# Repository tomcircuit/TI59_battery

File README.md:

# TI59_battery - LiPo Battery for TI-58/59 Calculators
 
This is my attempt at a LiPo-based battery pack for Texas Instruments Calculators that use the BP01 battery pack,  specifically the TI-58, TI-58C, and TI-59. The original NiCd packs are all dead by now, and rebuilding them is difficult, mostly because it requires cutting apart and then carefully re-assembling the plastic battery retention frame. I thought it would be fun to design a 3D printed housing and re-use the circuitry from my rechargeable HP LiPo battery pack. 

> LiPo chemistry has very specific care-and-feeding when it comes to recharging, **the original charger and charging circuitry will not suffice.**  For this reason, I include a USB receptacle, which allows for charging when removed from the calculator.

The basic idea is to use a gold-flashed (ENIG) PCB as the contact substrate, and mount the LiPo, USB micro B receptacle, and charging circuitry on the opposite side. A **charging LED** is placed on the same side as the contact pads, but in areas where there will be no mechanical interference. A 3D printed plastic holder ties it all together, and mates with the TI calculator case. 
 
## The Housing
I  have several original TI BP01 battery packs, so I was able to carefully measure them and create a 3D model using OpenSCAD. This is essentially a 3D solid 'programming language' which (for me) is much easier to work with than an interactive 3D CAD program. It took several iterations to arrive at a working holder design that would 3D print (FDM) reliably. Note that the holder is best printed "flat side down", but that this orientation is **not ideal** for the retention tab; it wants to break along the FDM layers. I have had good luck with PLA+ material, and even better results with PTEG. 

## The PCB 
The PCB holds the USB micro B connector, the charging circuitry, the protection circuitry, a connector for the LiPo battery, and most importantly the pads that mate with the contacts in the calculator.  The overall size of the PCB is 53mm x 28mm. The material is 1.6mm thick FR4. So that the contact pads do not  tarnish over time, I chose a gold-flash treatment (ENIG). 

The schematic and PCB were designed using KiCAD.

## The LiPo Battery
I wanted a 1S (3.7V) LiPo battery in the neighborhood of 1200mAhr that would fit within the confines of the original pack envelope. This led me to a size "103040" LiPo battery. 

## Putting It All Together
Pretty self-explanatory. I used 0805 size components to allow for easy hand-soldering. Note that D1 (LED) and Z1 (Zener) are both polarized, so pay attention to that. Soldering the USB connector requires a fine-tip iron and some patience, or a hot-air solder station. I use the latter with very good results. 

Connect the battery to the PCB, double-checking that the polarity of the LiPo is matching the **+** and **-** marks on the PCB. Place the battery into the holder in between the two pairs of screw bosses, and then press the PCB into place above it. Four #2 self-tapping stainless steel screws secure the PCB into the 3D printed holder.

## Charge It
Connect a micro-B cable to the board and charge the LiPo battery. The LED will stay lit during the charging process, and extinguish when it is completed. The charge current is about 220mA (0.2C for a 1200mAhr battery). You can adjust R1 to change the current (decrease R1 will increase charging current) if you need to. It took about three hours to charge my battery.

## Use It!
Install the pack into the calculator. Be very careful with the delicate latch retention tab when inserting and removing the holder, because it is fragile and prone to breakage. If it does break, you can usually re-attach the tab with Krazy Glue. Enjoy using your vintage TI programmable calculator!

>February 7. 2021
>Tom LeMense
> Written with [StackEdit](https://stackedit.io/). #

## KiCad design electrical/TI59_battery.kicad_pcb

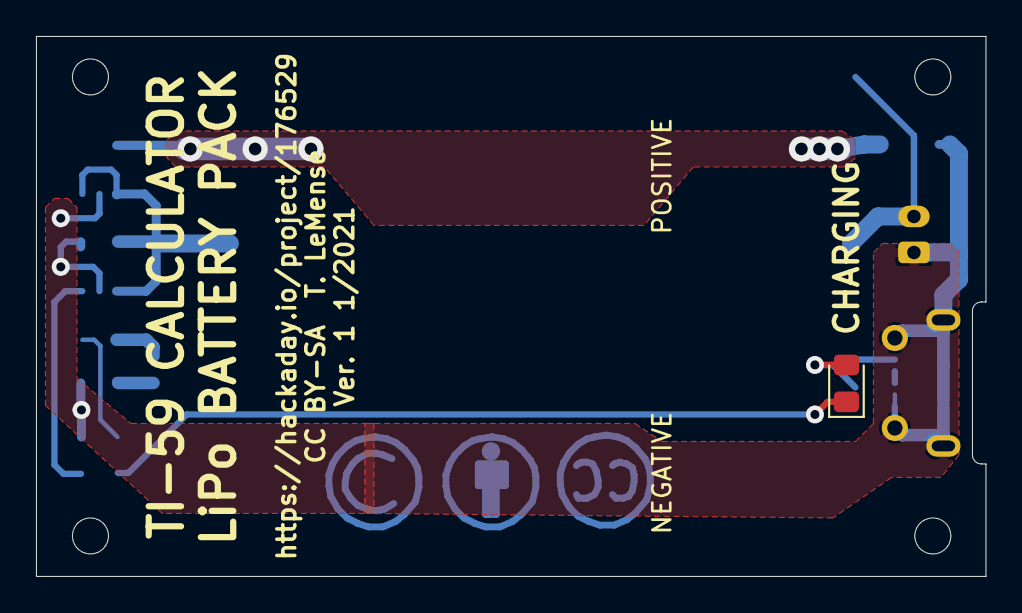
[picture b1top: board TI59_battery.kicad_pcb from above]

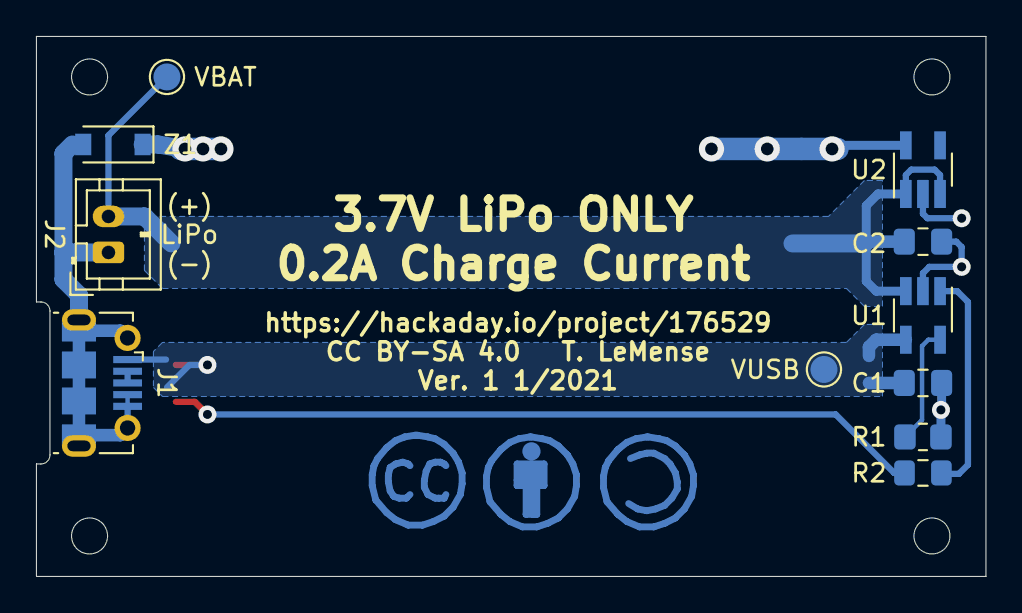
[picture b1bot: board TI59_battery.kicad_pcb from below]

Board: 2 copper layers, 52.8 x 30.0 mm, 16 parts (11 on the bottom side), 8 nets.

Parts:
C1, C2: 4.7uF; C_0805_2012Metric_Pad1.18x1.45mm_HandSolder
D1: LED; LED_0805_2012Metric_Pad1.15x1.40mm_HandSolder
H1, H2, H3, H4: MountingHole; MountingHole_2mm
J1: USB_B_Micro; USB_Micro-B_Molex-105017-0001
J2: JST PH 2mm; JST_PH_B2B-PH-K_1x02_P2.00mm_Vertical
R1: 4.7K; R_0805_2012Metric_Pad1.20x1.40mm_HandSolder
R2: 470; R_0805_2012Metric_Pad1.15x1.40mm_HandSolder
TP1: VUSB; TestPoint_Pad_D1.5mm
TP2: VBAT; TestPoint_Pad_D1.5mm
U1: MCP73831-2-OT; SOT-23-5_HandSoldering
U2: MAX40203AUK; SOT-23-5_HandSoldering
Z1: MMBZ5231; D_SOD-123

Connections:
/POS: U2.5, Z1.1
/VBAT: C2.1, J2.2, TP2.1, U1.3, U2.1, U2.3
/VUSB: C1.1, D1.2, J1.1, TP1.1, U1.4
GND: C1.2, C2.2, J1.4, J1.5, J1.6, J2.1, R1.2, U1.2, U2.2, Z1.2
unnamed: D1.1, R2.2
unnamed: J1.2, J1.3
unnamed: R1.1, U1.5
unnamed: R2.1, U1.1

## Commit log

2020-12-27 Delete TI59_pcb_outline.dxf
    removed old (and incorrect) PCB outline DXF file from mechnical directory
2020-12-27 work on PCB routing...
2021-01-14 Version 1 Release
    TI59 LiPo Battery Pack V1
    PCB and Schematic are frozen.
    Holder 0v5 is frozen
    Holder to be checked when PCB's are available.
2021-01-14 Update README.md
    PCB and holder status
2021-01-22 Additional JPG of LiPo Pack
2021-01-24 holder 0v6 and 0v7 upload
    0v6 fits into TI58 and TI59
    0v7 is an attempt to improve retention latch
2021-02-07 removed old v6 and v7 mech files
2021-02-07 updated README
    more info on the holder and final assembly. #2 SS screws indicated. Care with retention tab noted.
2021-02-07 removed 0v5 PCB guide DXF files
2021-02-07 TI-58/59 Holder v1
    Version 0v8 tested and ready for release, so bumped to v1.

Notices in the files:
electrical/TI59_battery.kicad_pcb:
CC BY-SA 4.0
CC BY-SA  T. LeMense
CC BY-SA 4.0 T. LeMense
